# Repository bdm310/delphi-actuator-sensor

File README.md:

# delphi-actuator-sensor
Replacement position sensor PCB for VAG/Porsche/Delphi HVAC actuators commonly used on the Porsche 955/9PA Cayenne, VW 7L Touareg, and perhaps Audi Q7. The original Alps resistive sensor usually fouls due to excessive grease application from the factory and appears to be a custom 4.7kOhm, 120 degree part that isn't purchasable. The closest sensor is the RDC503052A in the same mechanical package but it does not match the original electrical angle. This project matches the output of that sensor to the original range.

The connector pin spacing is 2.85mm and the pin headers used here are 2.54mm. Suggest soldering these on yourself as they need to be flush with the board and you can then tweak them as necessary to fit in the existing housing.

Non-comprehensive list of potentially applicable part numbers:
 - 955 624 901 01
 - 955 624 905 01
 - 955 624 902 01
 - 955 624 908 01
 - 955 624 909 01
 - 955 624 913 01
 - 955 624 912 01
 - 7L0907511AK (supersedes 7L0907511D)
 - 7L0907511AL (supersedes 7L0907511E)
 - 7L0907512G
 - 7L0907512F (supersedes 7L0907512)
 - 7L0907511AB
 - 7L0907511AD

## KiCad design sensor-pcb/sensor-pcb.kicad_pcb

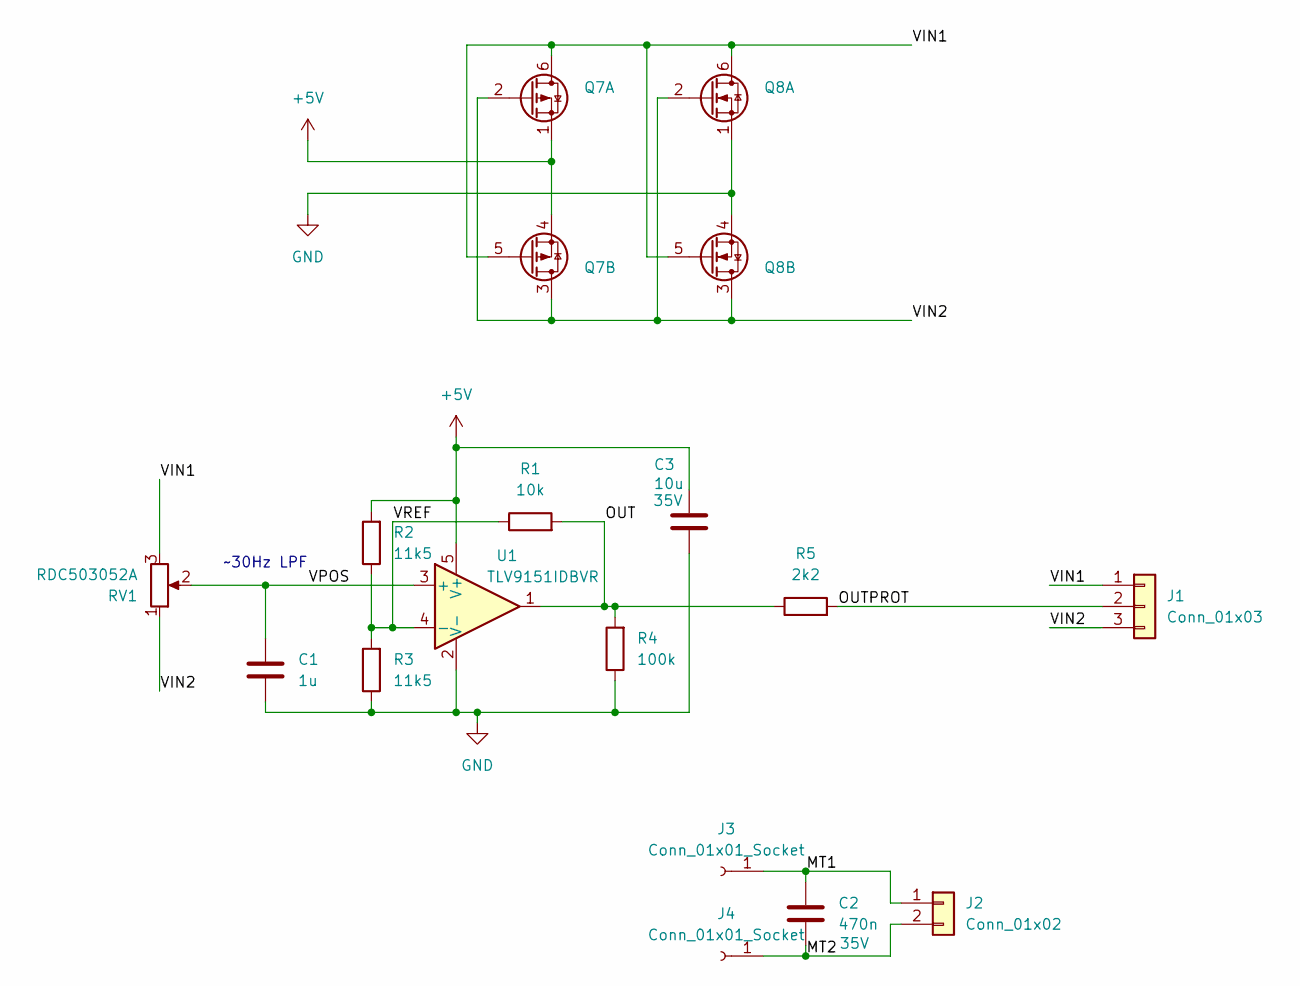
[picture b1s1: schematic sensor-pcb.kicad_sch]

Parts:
C1: 1u; C_0402_1005Metric; MPN GCM155C71A105KE38D
C2: 470n; C_1206_3216Metric; Voltage Rating 35V; MPN CGA5L2X7R1H474K160AA
C3: 10u; C_0805_2012Metric; Voltage Rating 35V; MPN GRM21BR61H106KE43L
J1: Conn_01x03; CONN03_22289031_MOL; MPN 22289031
J2: Conn_01x02; CONN02_22288021_MOL; MPN 22288021
J3, J4: Conn_01x01_Socket; 0666-0-15-15-32-27-10-0; MPN 0666-0-15-15-32-27-10-0
Q7: BSS84DW-7-F; SOT-363_SC-70-6; MPN BSS84DW-7-F
Q8: 2N7002DW; SOT-363_SC-70-6; MPN 2N7002DW
R1: 10k; R_0402_1005Metric; MPN RMCF0402FT10K0
R2, R3: 11k5; R_0402_1005Metric; MPN RMCF0402FT11K5
R4: 100k; R_0402_1005Metric; MPN RMCF0402FT100K
R5: 2k2; R_0402_1005Metric; MPN RMCF0402FT2K20
RV1: RDC503052A; alps-rcd50-smd; MPN RDC503052A
U1: TLV9151IDBVR; SOT-23-5; MPN TLV9151IDBVR

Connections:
+5V: C3.1, Q7.1 (S), Q7.4 (S), R2.2, U1.5 (V+)
/MT1: C2.1, J2.1, J3.1
/MT2: C2.2, J2.2, J4.1
/OUT: R1.2, R4.2, R5.1, U1.1
/OUTPROT: J1.2, R5.2
/VIN1: J1.1, Q7.5 (G), Q7.6 (D), Q8.5 (G), Q8.6 (D), RV1.3
/VIN2: J1.3, Q7.2 (G), Q7.3 (D), Q8.2 (G), Q8.3 (D), RV1.1
/VPOS: C1.1, RV1.2, U1.3 (+)
/VREF: R1.1, R2.1, R3.2, U1.4 (-)
GND: C1.2, C3.2, Q8.1 (S), Q8.4 (S), R3.1, R4.1, U1.2 (V-)

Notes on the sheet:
~30Hz LPF

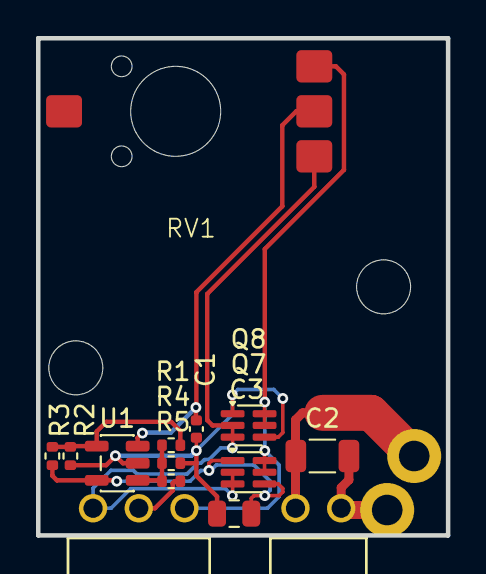
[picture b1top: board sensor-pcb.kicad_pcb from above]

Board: 2 copper layers, 22.8 x 27.6 mm, 19 parts (0 on the bottom side), 10 nets.

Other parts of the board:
MH1: MountingHole_5mm
MH2, MH3: MountingHole_3mm

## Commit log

2026-01-25 Add board image
2026-02-11 Fix flipped power pins
2026-02-11 Reverse direction
2026-02-12 Change design to allow arbitrary polarity
